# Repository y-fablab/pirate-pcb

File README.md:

# pirate-pcb

PCB for Pirate Box

## Documentation

* [Schematics](./doc/schematics.pdf)
* [2D Preview](./doc/preview-2d.jpeg)

## Warnings

The WEMOS/LOLIN D1 mini is directly powered by the battery. We typically use 4 AA batteries. Therefore, the power voltage is 6V instead of the 5V usually required. This does not cause any problem, provided that:

1. On the D1 mini, this voltage only powers the 3.3V regulator. This is the case for classic versions of D1 mini where both the CH340 and the SPI memory are powered by 3.3V.
2. When powered through USB, the power goes through a diode. This is the case for all D1 mini versions up to 3.x.x. However, on version 4.0.0, there is no diode and the 6V battery would be connected directly to the USB 5V line, which is not good. Do not use D1 mini version 4.0.0+ on this board.

We recommend using D1 mini v3.x.x and verifying that it has a CH340 chip.

## License

Copyright (c) 2023 [y-fablab.ch](https://www.y-fablab.ch)

Licensed under the [Creative Commons CC-BY 4.0 License](https://creativecommons.org/licenses/by/4.0/)

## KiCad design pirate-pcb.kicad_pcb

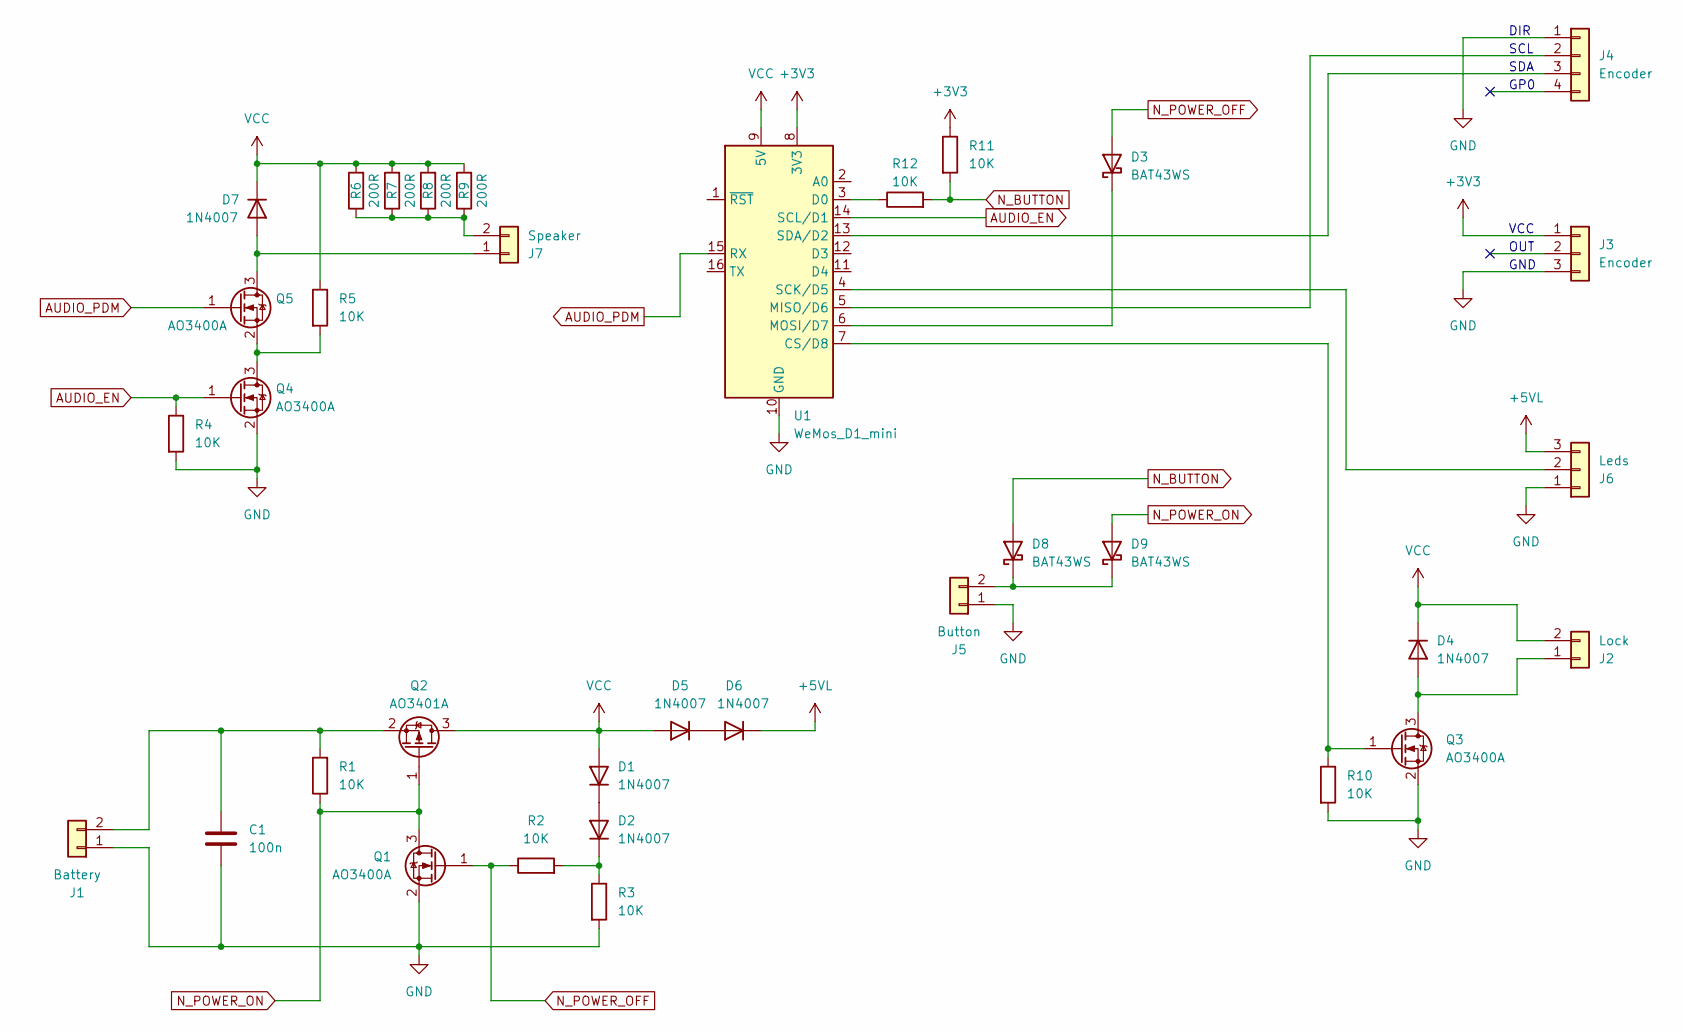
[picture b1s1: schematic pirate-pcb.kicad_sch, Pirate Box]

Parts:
C1: 100n; C_0603_1608Metric_Pad1.08x0.95mm_HandSolder
D1, D2, D4, D5, D6, D7: 1N4007; D_SMA
D3, D8, D9: BAT43WS; D_SOD-323_HandSoldering
J1: Battery; TerminalBlock_KaiFeng_KF141R-2_1x02_P2.54mm
J2: Lock; JST_PH_B2B-PH-K_1x02_P2.00mm_Vertical
J3: Encoder; PinHeader_1x03_P2.54mm_Vertical
J4: Encoder; PinHeader_1x04_P2.54mm_Vertical
J5: Button; PinHeader_1x02_P2.54mm_Vertical
J6: Leds; PinHeader_1x03_P2.54mm_Vertical
J7: Speaker; PinHeader_1x02_P2.54mm_Vertical
Q1, Q3, Q4, Q5: AO3400A; SOT-23
Q2: AO3401A; SOT-23
R1, R2, R3, R4, R5, R10, R11, R12: 10K; R_0603_1608Metric_Pad0.98x0.95mm_HandSolder
R6, R7, R8, R9: 200R; R_0603_1608Metric_Pad0.98x0.95mm_HandSolder
U1: WeMos_D1_mini; WEMOS_D1_mini_light

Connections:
+3V3: J3.1, R11.1, U1.8 (3V3)
+5VL: D6.1 (K), J6.3
AUDIO_EN: Q4.1 (G), R4.1, U1.14 (SCL/D1)
AUDIO_PDM: Q5.1 (G), U1.15 (RX)
GND: C1.2, J1.1, J3.3, J4.1, J5.1, J6.1, Q1.2 (S), Q3.2 (S), Q4.2 (S), R3.2, R4.2, R10.2, U1.10 (GND)
N_BUTTON: D8.2 (A), R11.2, R12.2
N_POWER_OFF: D3.2 (A), Q1.1 (G), R2.1
N_POWER_ON: D9.2 (A), Q1.3 (D), Q2.1 (G), R1.1
unnamed: D1.1 (K), D2.2 (A)
unnamed: D2.1 (K), R2.2, R3.1
unnamed: D3.1 (K), U1.6 (MOSI/D7)
unnamed: D4.2 (A), J2.1, Q3.3 (D)
unnamed: D5.1 (K), D6.2 (A)
unnamed: D7.2 (A), J7.1, Q5.3 (D)
unnamed: D8.1 (K), D9.1 (K), J5.2
unnamed: C1.1, J1.2, Q2.2 (S), R1.2
unnamed: J4.2, U1.5 (MISO/D6)
unnamed: J4.3, U1.13 (SDA/D2)
unnamed: J6.2, U1.4 (SCK/D5)
unnamed: J7.2, R6.1, R7.1, R8.1, R9.1
unnamed: Q3.1 (G), R10.1, U1.7 (CS/D8)
unnamed: Q4.3 (D), Q5.2 (S), R5.2
unnamed: R12.1, U1.3 (D0)
VCC: D1.2 (A), D4.1 (K), D5.2 (A), D7.1 (K), J2.2, Q2.3 (D), R5.1, R6.2, R7.2, R8.2, R9.2, U1.9 (5V)

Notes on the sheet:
OUT
GND
DIR
GP0
SDA
VCC
SCL

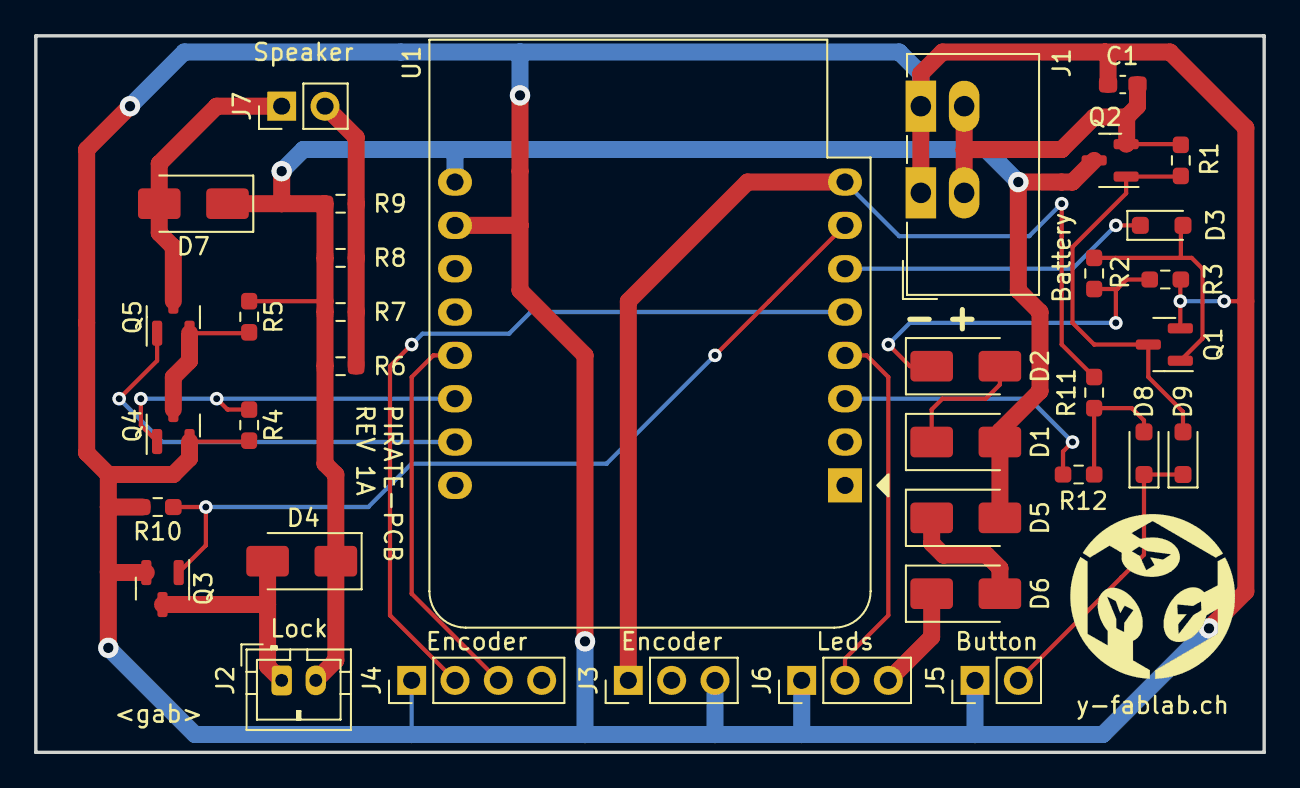
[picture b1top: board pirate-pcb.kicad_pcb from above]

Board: 2 copper layers, 72.0 x 42.0 mm, 36 parts (0 on the bottom side), 24 nets.

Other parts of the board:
G1: LOGO; y-fablab_logo_10mm

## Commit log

2023-07-09 revision 1A
2023-07-09 add prod files
2023-07-10 add README
2023-07-10 add license
2023-07-10 add warnings
